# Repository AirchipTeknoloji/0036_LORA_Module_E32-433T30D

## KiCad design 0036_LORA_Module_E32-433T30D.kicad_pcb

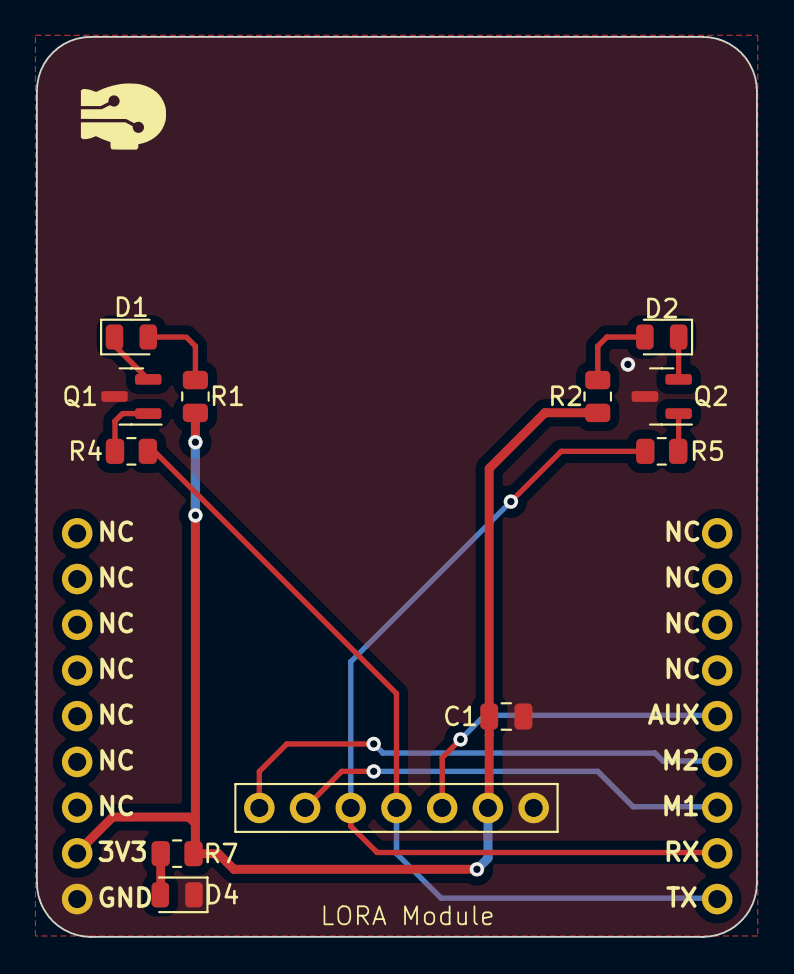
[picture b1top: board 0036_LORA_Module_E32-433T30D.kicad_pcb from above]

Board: 2 copper layers, 40.0 x 50.0 mm, 13 parts (0 on the bottom side), 14 nets.

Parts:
C1: C; C_0805_2012Metric
D1, D2, D4: LED; LED_0805_2012Metric
J1: Conn_01x07_Pin; PinHeader_1x07_P2.54mm_Vertical
Q1: MMBT3906; SOT-23
Q2: 3906; SOT-23
R1, R2, R7: R; R_0805_2012Metric
R4, R5: 0r; R_0805_2012Metric
U1: pin_header_5-3

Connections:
+3V3: C1.1, J1.6 (VCC), R1.1, R2.1, R7.2, U1.8
AUX: J1.5 (AUX), U1.14
GND: C1.2, D4.1 (K), J1.7 (GND), Q1.3 (C), Q2.3 (C), U1.9
M1: J1.2 (M1), U1.12
M2: J1.1 (M0), U1.13
unnamed: D1.2 (A), R1.2
unnamed: D1.1 (K), Q1.2 (E)
unnamed: D2.2 (A), R2.2
unnamed: D2.1 (K), Q2.2 (E)
unnamed: D4.2 (A), R7.1
unnamed: Q1.1 (B), R4.1
unnamed: Q2.1 (B), R5.1
RX: J1.3 (RX), R5.2, U1.11
TX: J1.4 (TX), R4.2, U1.10
